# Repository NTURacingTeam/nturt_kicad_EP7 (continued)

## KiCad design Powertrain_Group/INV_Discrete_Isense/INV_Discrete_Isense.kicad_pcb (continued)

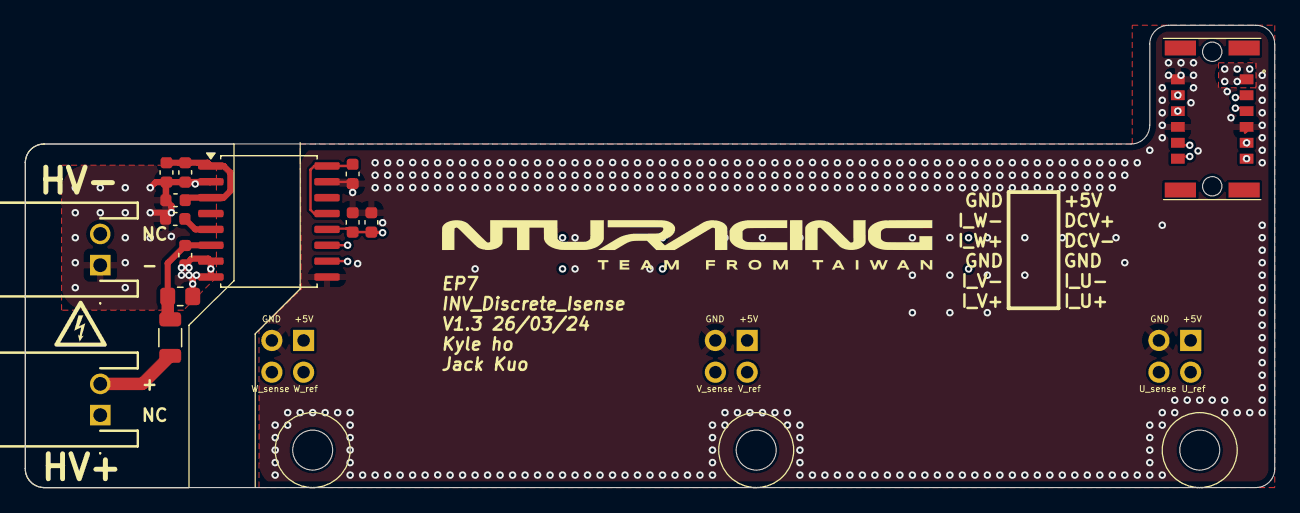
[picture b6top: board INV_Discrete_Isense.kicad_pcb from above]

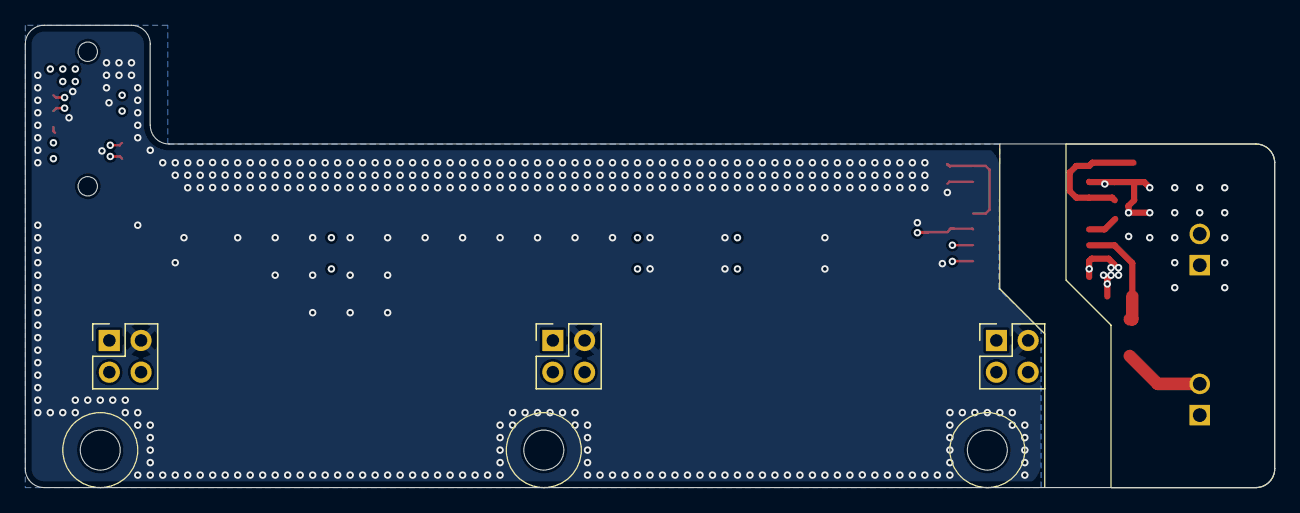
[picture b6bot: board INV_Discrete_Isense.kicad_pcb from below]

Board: 4 copper layers, 100.0 x 37.0 mm, 20 parts (3 on the bottom side), 16 nets.

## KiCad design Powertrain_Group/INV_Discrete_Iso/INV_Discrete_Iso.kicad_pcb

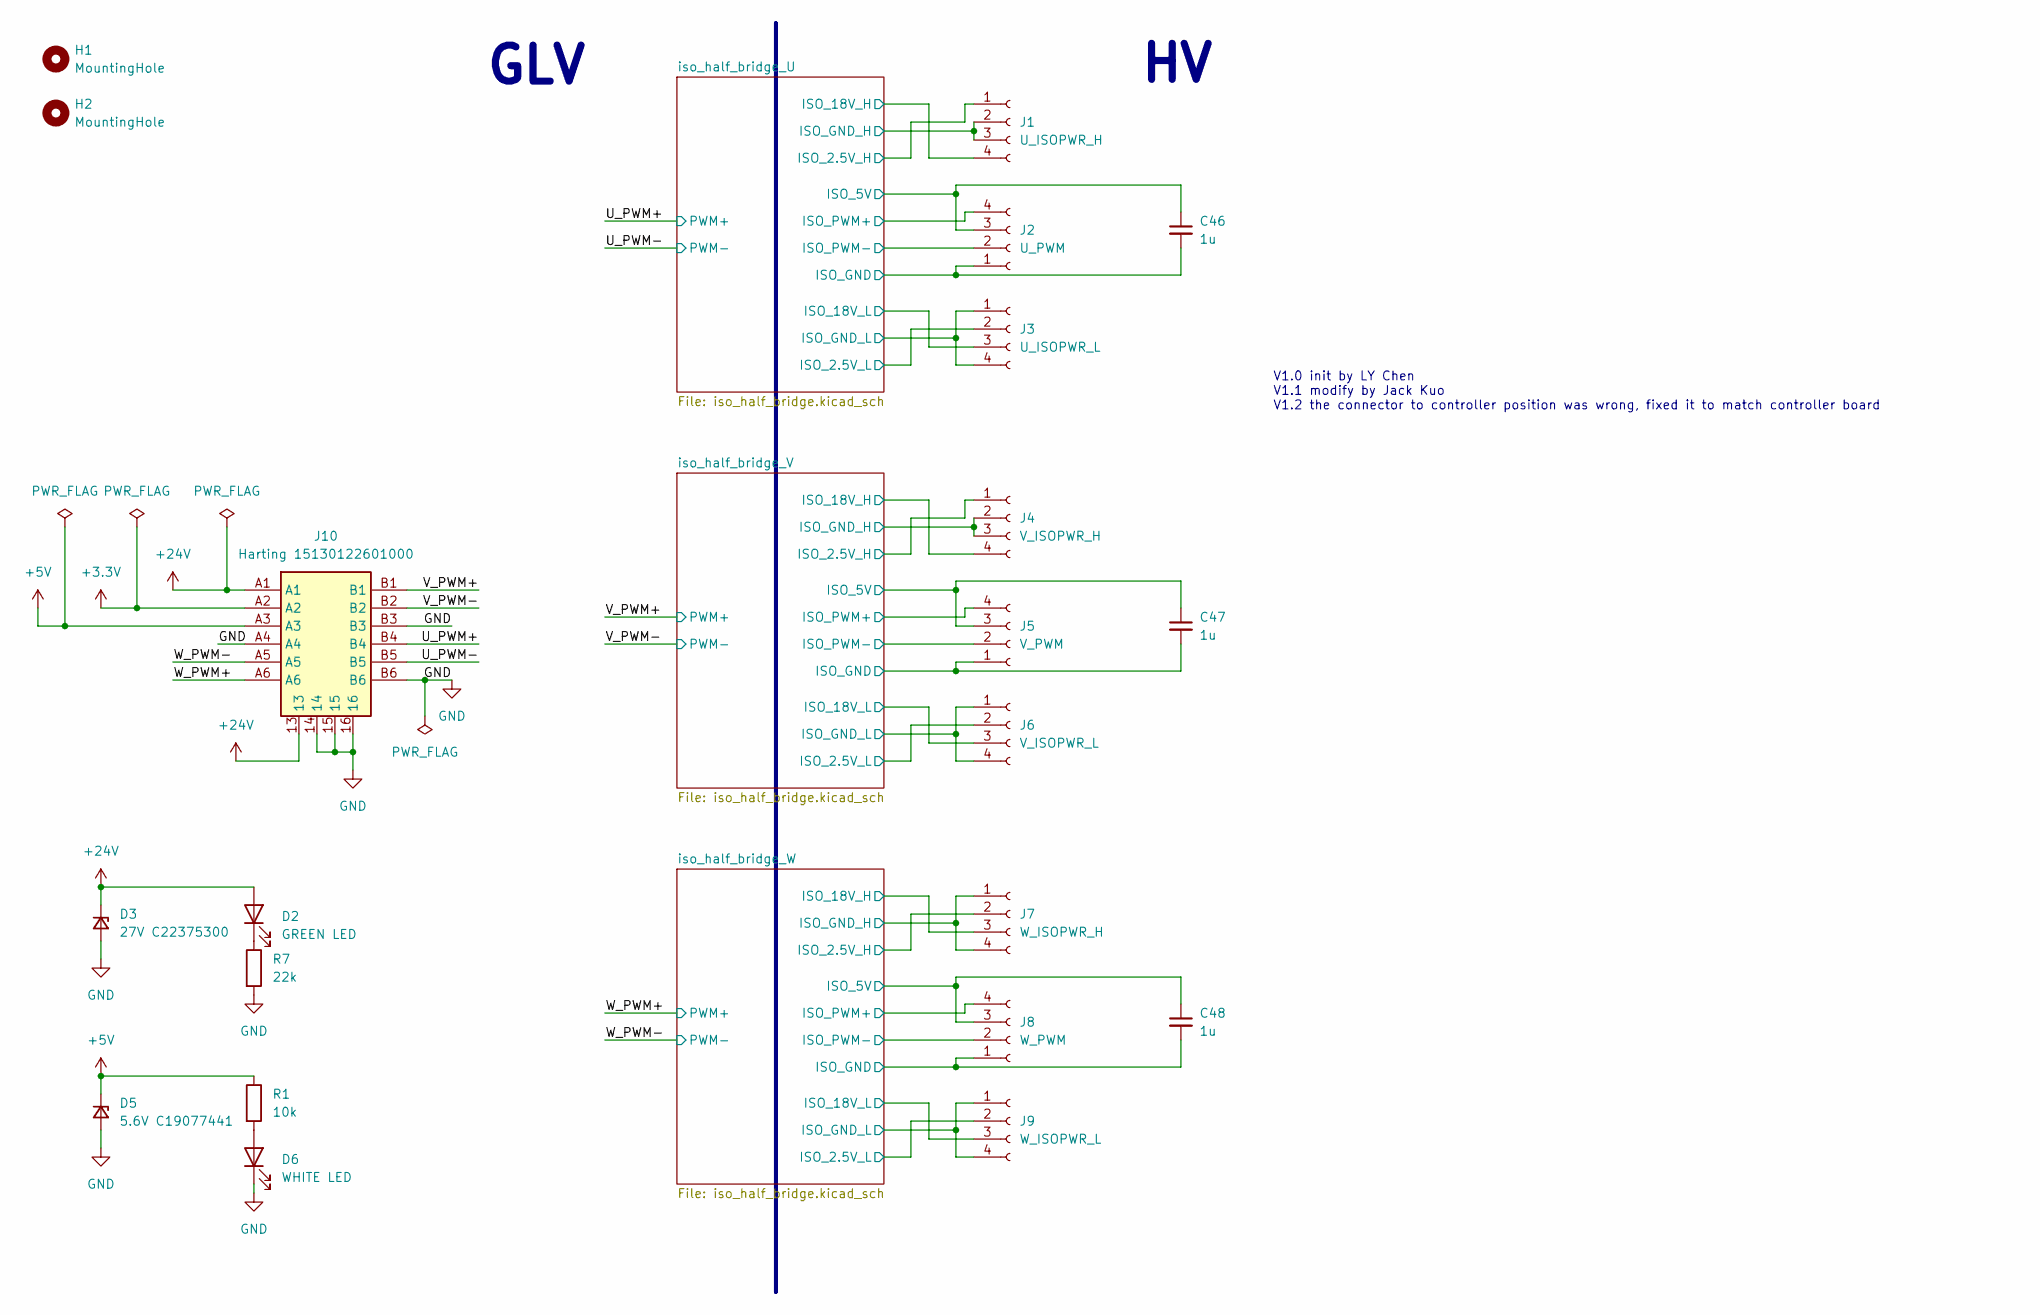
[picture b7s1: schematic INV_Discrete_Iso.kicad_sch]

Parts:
C46, C47, C48: 1u; C_0603_1608Metric
D2: GREEN LED; LED_0603_1608Metric
D3: 27V C22375300; D_SOD-323
D5: 5.6V C19077441; D_SOD-323
D6: WHITE LED; LED_0603_1608Metric
H1, H2: MountingHole; MountingHole_3.2mm_M3
J1: U_ISOPWR_H; PinSocket_2x02_P2.54mm_Vertical_SMD
J2: U_PWM; PinSocket_2x02_P2.54mm_Vertical_SMD
J3: U_ISOPWR_L; PinSocket_2x02_P2.54mm_Vertical_SMD
J4: V_ISOPWR_H; PinSocket_2x02_P2.54mm_Vertical_SMD
J5: V_PWM; PinSocket_2x02_P2.54mm_Vertical_SMD
J6: V_ISOPWR_L; PinSocket_2x02_P2.54mm_Vertical_SMD
J7: W_ISOPWR_H; PinSocket_2x02_P2.54mm_Vertical_SMD
J8: W_PWM; PinSocket_2x02_P2.54mm_Vertical_SMD
J9: W_ISOPWR_L; PinSocket_2x02_P2.54mm_Vertical_SMD
J10: Harting 15130122601000; Harting_15130122601000; Mouser Part Number 617-15130122601000
R1: 10k; R_0402_1005Metric
R7: 22k; R_0402_1005Metric

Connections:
+3.3V: J10.A2; also elsewhere on the board
+5V: D5.1 (K), J10.A3, R1.1; also elsewhere on the board
+24V: D2.2 (A), D3.1 (K), J10.13, J10.A1; also elsewhere on the board
/U_PWM+: J10.B4; also elsewhere on the board
/U_PWM-: J10.B5; also elsewhere on the board
/V_PWM+: J10.B1; also elsewhere on the board
/V_PWM-: J10.B2; also elsewhere on the board
/W_PWM+: J10.A6; also elsewhere on the board
/W_PWM-: J10.A5; also elsewhere on the board
/iso_half_bridge_U/ISO_2.5V_H: J1.1; also elsewhere on the board
/iso_half_bridge_U/ISO_2.5V_L: J3.2; also elsewhere on the board
/iso_half_bridge_U/ISO_5V: C46.1, J2.3; also elsewhere on the board
/iso_half_bridge_U/ISO_18V_H: J1.4; also elsewhere on the board
/iso_half_bridge_U/ISO_18V_L: J3.3; also elsewhere on the board
/iso_half_bridge_U/ISO_GND: C46.2, J2.1; also elsewhere on the board
/iso_half_bridge_U/ISO_GND_H: J1.2, J1.3; also elsewhere on the board
/iso_half_bridge_U/ISO_GND_L: J3.1, J3.4; also elsewhere on the board
/iso_half_bridge_U/ISO_PWM+: J2.4; also elsewhere on the board
/iso_half_bridge_U/ISO_PWM-: J2.2; also elsewhere on the board
/iso_half_bridge_V/ISO_2.5V_H: J4.1; also elsewhere on the board
/iso_half_bridge_V/ISO_2.5V_L: J6.2; also elsewhere on the board
/iso_half_bridge_V/ISO_5V: C47.1, J5.3; also elsewhere on the board
/iso_half_bridge_V/ISO_18V_H: J4.4; also elsewhere on the board
/iso_half_bridge_V/ISO_18V_L: J6.3; also elsewhere on the board
/iso_half_bridge_V/ISO_GND: C47.2, J5.1; also elsewhere on the board
/iso_half_bridge_V/ISO_GND_H: J4.2, J4.3; also elsewhere on the board
/iso_half_bridge_V/ISO_GND_L: J6.1, J6.4; also elsewhere on the board
/iso_half_bridge_V/ISO_PWM+: J5.4; also elsewhere on the board
/iso_half_bridge_V/ISO_PWM-: J5.2; also elsewhere on the board
/iso_half_bridge_W/ISO_2.5V_H: J7.2; also elsewhere on the board
/iso_half_bridge_W/ISO_2.5V_L: J9.2; also elsewhere on the board
/iso_half_bridge_W/ISO_5V: C48.1, J8.3; also elsewhere on the board
/iso_half_bridge_W/ISO_18V_H: J7.3; also elsewhere on the board
/iso_half_bridge_W/ISO_18V_L: J9.3; also elsewhere on the board
/iso_half_bridge_W/ISO_GND: C48.2, J8.1; also elsewhere on the board
/iso_half_bridge_W/ISO_GND_H: J7.1, J7.4; also elsewhere on the board
/iso_half_bridge_W/ISO_GND_L: J9.1, J9.4; also elsewhere on the board
/iso_half_bridge_W/ISO_PWM+: J8.4; also elsewhere on the board
/iso_half_bridge_W/ISO_PWM-: J8.2; also elsewhere on the board
GND: D3.2 (A), D5.2 (A), D6.1 (K), J10.14, J10.15, J10.16, J10.A4, J10.B3, J10.B6, R7.2; also elsewhere on the board
unnamed: D2.1 (K), R7.1
unnamed: D6.2 (A), R1.2

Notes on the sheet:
V1.0 init by LY Chen V1.1 modify by Jack Kuo V1.2 the connector to controller position was wrong, fixed it to match controller board
GLV

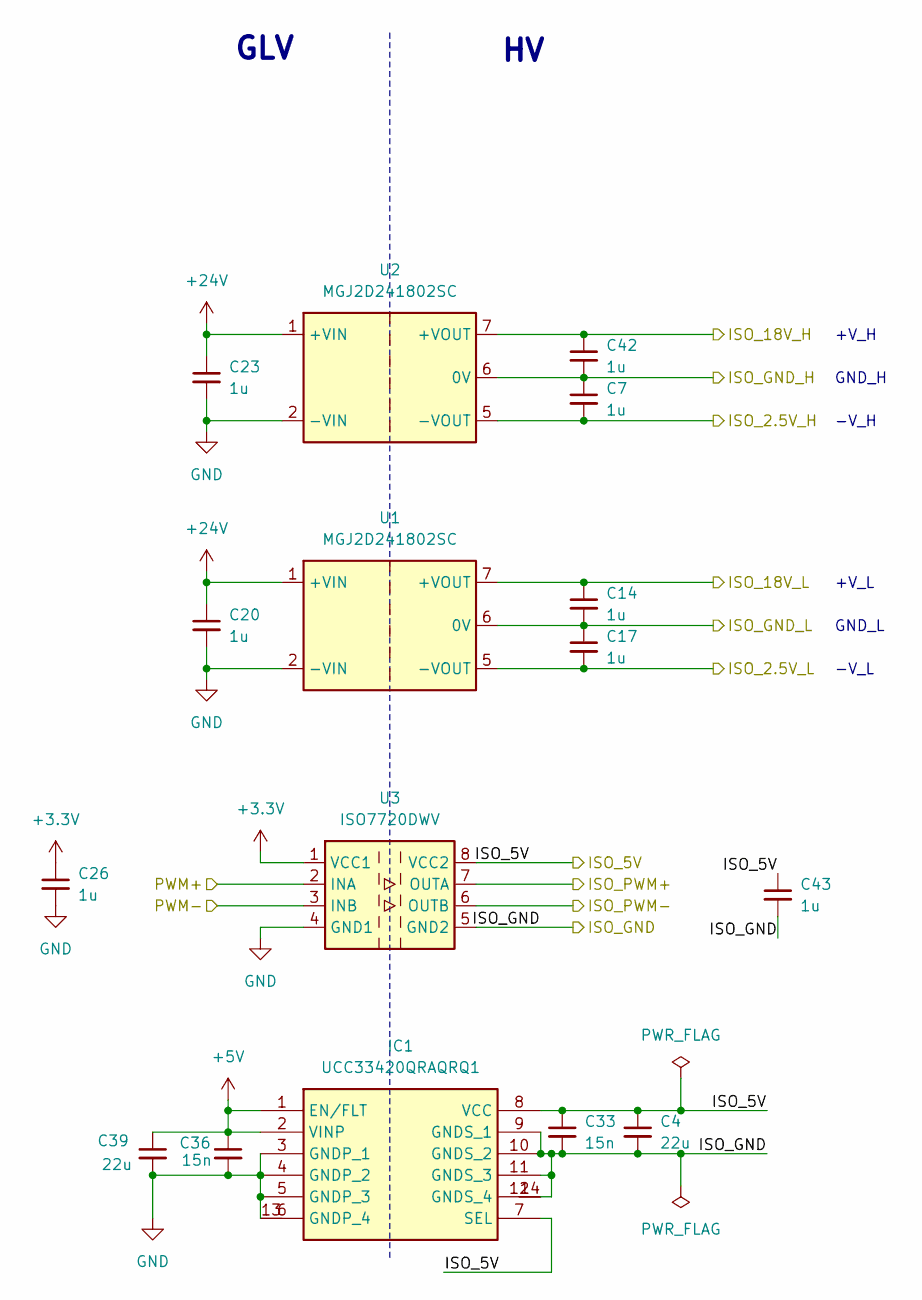
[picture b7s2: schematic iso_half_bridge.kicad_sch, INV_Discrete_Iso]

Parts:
C4, C39: 22u; C_0805_2012Metric
C7, C14, C17, C42: 1u; C_0603_1608Metric_Pad1.08x0.95mm_HandSolder
C20, C23, C26, C43: 1u; C_0603_1608Metric
C33, C36: 15n; C_0603_1608Metric_Pad1.08x0.95mm_HandSolder
IC1: UCC33420QRAQRQ1; UCC33020; Mouser Part Number 595-UCC33420QRAQRQ1
U1, U2: MGJ2D241802SC; Converter_DCDC_Murata_MGJ2DxxxxxxSC_THT
U3: ISO7720DWV; SOIC-8_7.5x5.85mm_P1.27mm

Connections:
+3.3V: C26.1, U3.1 (VCC1); also elsewhere on the board
+5V: C36.1, C39.1, IC1.1 (EN/FLT), IC1.2 (VINP); also elsewhere on the board
+24V: C20.1, C23.1, U1.1 (+VIN), U2.1 (+VIN); also elsewhere on the board
/U_PWM+: U3.2 (INA); also elsewhere on the board
/U_PWM-: U3.3 (INB); also elsewhere on the board
/iso_half_bridge_U/ISO_2.5V_H: C7.2, U2.5 (-VOUT); also elsewhere on the board
/iso_half_bridge_U/ISO_2.5V_L: C17.2, U1.5 (-VOUT); also elsewhere on the board
/iso_half_bridge_U/ISO_5V: C4.1, C33.1, C43.1, IC1.7 (SEL), IC1.8 (VCC), U3.8 (VCC2); also elsewhere on the board
/iso_half_bridge_U/ISO_18V_H: C42.1, U2.7 (+VOUT); also elsewhere on the board
/iso_half_bridge_U/ISO_18V_L: C14.1, U1.7 (+VOUT); also elsewhere on the board
/iso_half_bridge_U/ISO_GND: C4.2, C33.2, C43.2, IC1.9 (GNDS_1), IC1.10 (GNDS_2), IC1.11 (GNDS_3), IC1.12 (GNDS_4), IC1.14, U3.5 (GND2); also elsewhere on the board
/iso_half_bridge_U/ISO_GND_H: C7.1, C42.2, U2.6 (0V); also elsewhere on the board
/iso_half_bridge_U/ISO_GND_L: C14.2, C17.1, U1.6 (0V); also elsewhere on the board
/iso_half_bridge_U/ISO_PWM+: U3.7 (OUTA); also elsewhere on the board
/iso_half_bridge_U/ISO_PWM-: U3.6 (OUTB); also elsewhere on the board
GND: C20.2, C23.2, C26.2, C36.2, C39.2, IC1.3 (GNDP_1), IC1.4 (GNDP_2), IC1.5 (GNDP_3), IC1.6 (GNDP_4), IC1.13, U1.2 (-VIN), U2.2 (-VIN), U3.4 (GND1); also elsewhere on the board

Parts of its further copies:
C3, C6, C8, C24, C27, C28, C44, C45: 1u; C_0603_1608Metric
C5, C18, C25, C37: 22u; C_0805_2012Metric
C9, C10, C29, C30: 15n; C_0603_1608Metric_Pad1.08x0.95mm_HandSolder
C12, C13, C15, C16, C31, C32, C34, C35: 1u; C_0603_1608Metric_Pad1.08x0.95mm_HandSolder
IC2, IC4: UCC33420QRAQRQ1; UCC33020; Mouser Part Number 595-UCC33420QRAQRQ1
U4, U5, U7, U8: MGJ2D241802SC; Converter_DCDC_Murata_MGJ2DxxxxxxSC_THT
U6, U9: ISO7720DWV; SOIC-8_7.5x5.85mm_P1.27mm

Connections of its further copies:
+3.3V: C3.1, C24.1, U6.1 (VCC1), U9.1 (VCC1); also elsewhere on the board
+5V: C5.1, C9.1, C25.1, C29.1, IC2.1 (EN/FLT), IC2.2 (VINP), IC4.1 (EN/FLT), IC4.2 (VINP); also elsewhere on the board
+24V: C6.1, C8.1, C27.1, C28.1, U4.1 (+VIN), U5.1 (+VIN), U7.1 (+VIN), U8.1 (+VIN); also elsewhere on the board
/V_PWM+: U6.2 (INA); also elsewhere on the board
/V_PWM-: U6.3 (INB); also elsewhere on the board
/W_PWM+: U9.2 (INA); also elsewhere on the board
/W_PWM-: U9.3 (INB); also elsewhere on the board
/iso_half_bridge_V/ISO_2.5V_H: C13.2, U4.5 (-VOUT); also elsewhere on the board
/iso_half_bridge_V/ISO_2.5V_L: C16.2, U5.5 (-VOUT); also elsewhere on the board
/iso_half_bridge_V/ISO_5V: C10.1, C18.1, C44.1, IC2.7 (SEL), IC2.8 (VCC), U6.8 (VCC2); also elsewhere on the board
/iso_half_bridge_V/ISO_18V_H: C12.1, U4.7 (+VOUT); also elsewhere on the board
/iso_half_bridge_V/ISO_18V_L: C15.1, U5.7 (+VOUT); also elsewhere on the board
/iso_half_bridge_V/ISO_GND: C10.2, C18.2, C44.2, IC2.9 (GNDS_1), IC2.10 (GNDS_2), IC2.11 (GNDS_3), IC2.12 (GNDS_4), IC2.14, U6.5 (GND2); also elsewhere on the board
/iso_half_bridge_V/ISO_GND_H: C12.2, C13.1, U4.6 (0V); also elsewhere on the board
/iso_half_bridge_V/ISO_GND_L: C15.2, C16.1, U5.6 (0V); also elsewhere on the board
/iso_half_bridge_V/ISO_PWM+: U6.7 (OUTA); also elsewhere on the board
/iso_half_bridge_V/ISO_PWM-: U6.6 (OUTB); also elsewhere on the board
/iso_half_bridge_W/ISO_2.5V_H: C32.2, U7.5 (-VOUT); also elsewhere on the board
/iso_half_bridge_W/ISO_2.5V_L: C35.2, U8.5 (-VOUT); also elsewhere on the board
/iso_half_bridge_W/ISO_5V: C30.1, C37.1, C45.1, IC4.7 (SEL), IC4.8 (VCC), U9.8 (VCC2); also elsewhere on the board
/iso_half_bridge_W/ISO_18V_H: C31.1, U7.7 (+VOUT); also elsewhere on the board
/iso_half_bridge_W/ISO_18V_L: C34.1, U8.7 (+VOUT); also elsewhere on the board
/iso_half_bridge_W/ISO_GND: C30.2, C37.2, C45.2, IC4.9 (GNDS_1), IC4.10 (GNDS_2), IC4.11 (GNDS_3), IC4.12 (GNDS_4), IC4.14, U9.5 (GND2); also elsewhere on the board
/iso_half_bridge_W/ISO_GND_H: C31.2, C32.1, U7.6 (0V); also elsewhere on the board
/iso_half_bridge_W/ISO_GND_L: C34.2, C35.1, U8.6 (0V); also elsewhere on the board
/iso_half_bridge_W/ISO_PWM+: U9.7 (OUTA); also elsewhere on the board
/iso_half_bridge_W/ISO_PWM-: U9.6 (OUTB); also elsewhere on the board
GND: C3.2, C5.2, C6.2, C8.2, C9.2, C24.2, C25.2, C27.2, C28.2, C29.2, IC2.3 (GNDP_1), IC2.4 (GNDP_2), IC2.5 (GNDP_3), IC2.6 (GNDP_4), IC2.13, IC4.3 (GNDP_1), IC4.4 (GNDP_2), IC4.5 (GNDP_3), IC4.6 (GNDP_4), IC4.13, U4.2 (-VIN), U5.2 (-VIN), U6.4 (GND1), U7.2 (-VIN), U8.2 (-VIN), U9.4 (GND1); also elsewhere on the board

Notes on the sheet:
-V_L
GND_H
+V_H
GND_L
GLV
+V_L
-V_H

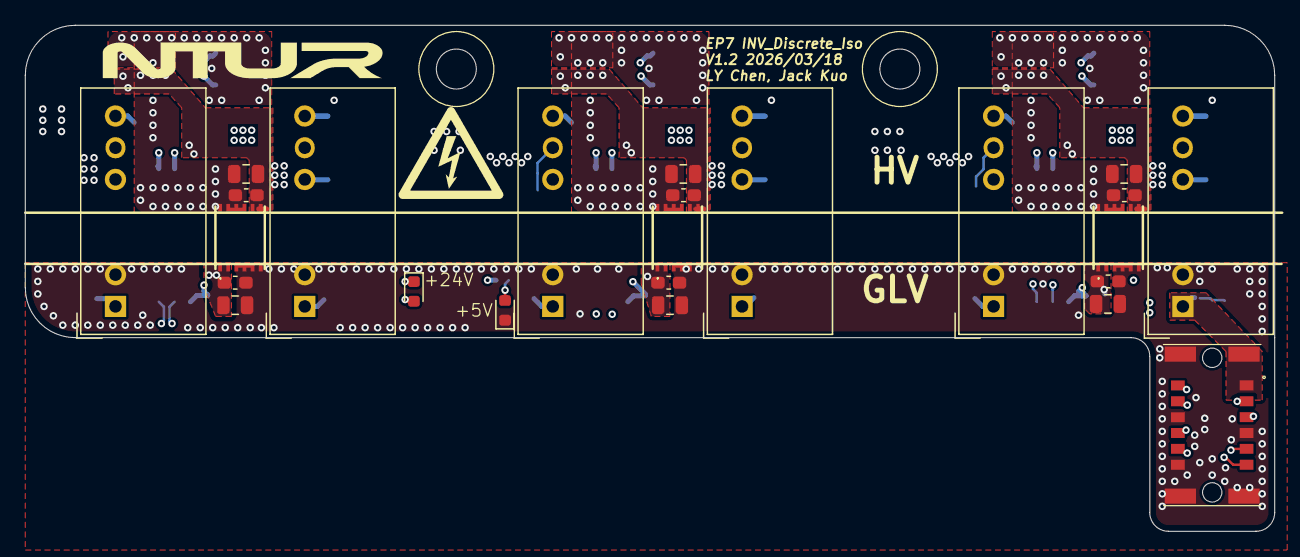
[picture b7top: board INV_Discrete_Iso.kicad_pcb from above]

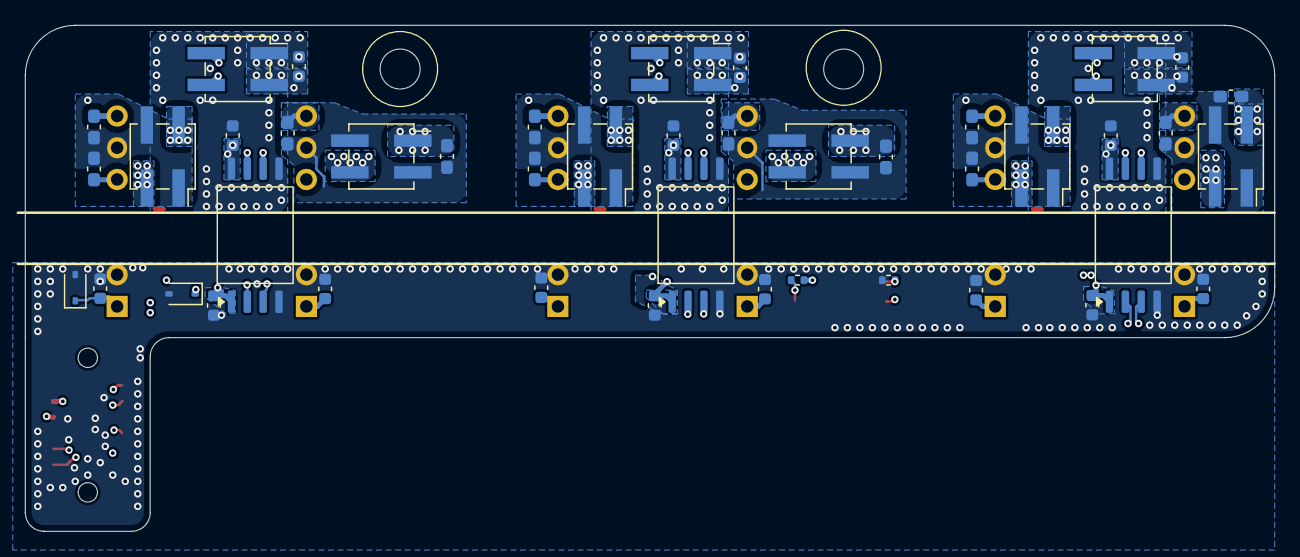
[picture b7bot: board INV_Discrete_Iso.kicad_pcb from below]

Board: 4 copper layers, 100.0 x 40.5 mm, 69 parts (43 on the bottom side), 42 nets.

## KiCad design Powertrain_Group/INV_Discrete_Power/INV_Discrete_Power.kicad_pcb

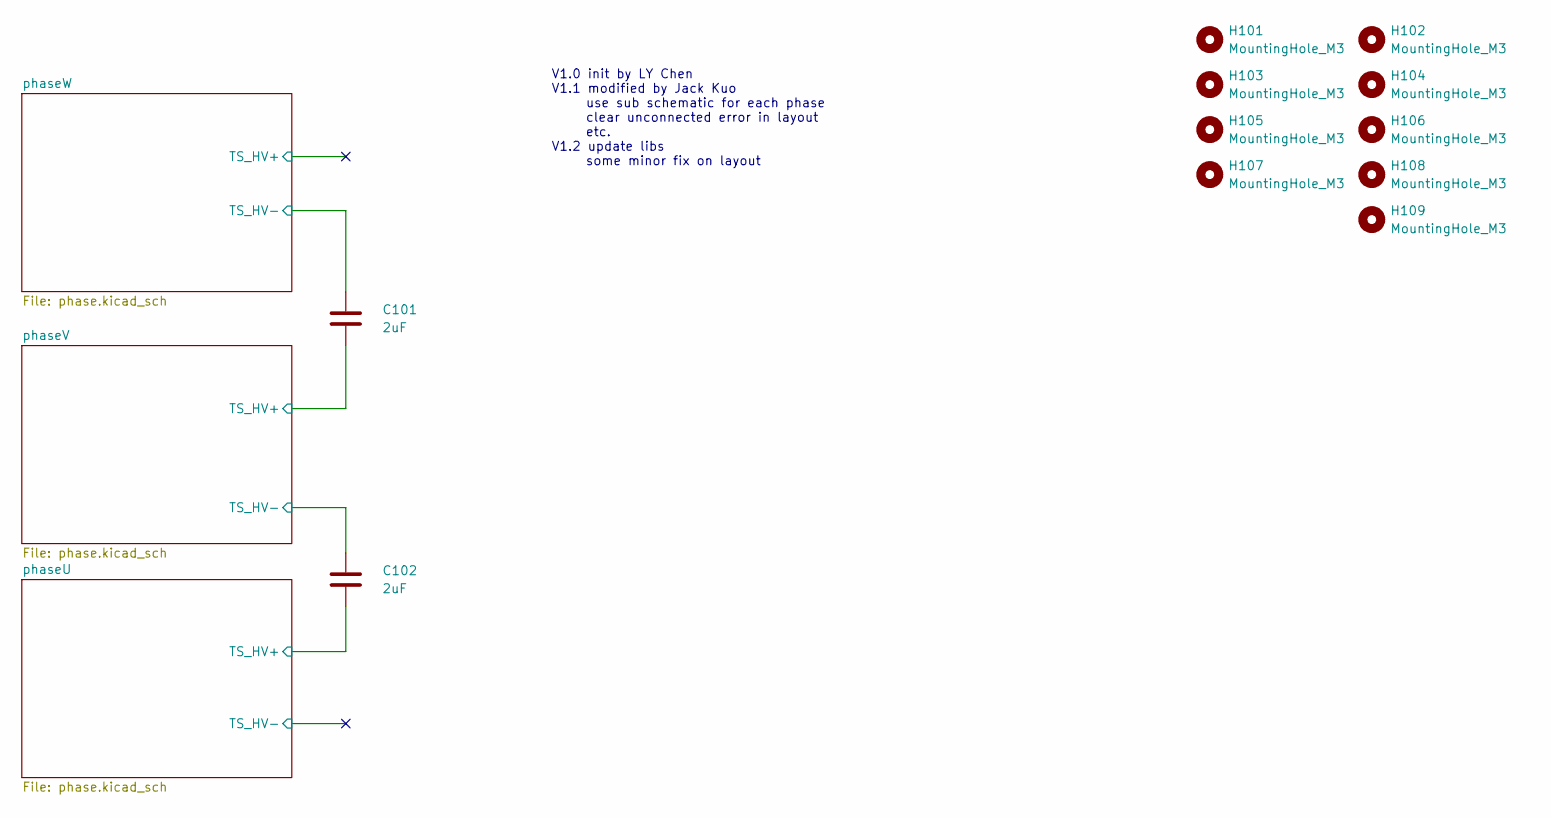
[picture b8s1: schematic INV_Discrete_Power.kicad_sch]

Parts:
C101, C102: 2uF; TDK_Ceralink_FA2
H101, H102, H103, H104, H105, H106, H107, H108, H109: MountingHole_M3; MountingHole_3.2mm_M3_ISO14580

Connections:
/phaseU/TS_HV+: C102.2; also elsewhere on the board
/phaseV/TS_HV+: C101.2; also elsewhere on the board
/phaseV/TS_HV-: C102.1; also elsewhere on the board
/phaseW/TS_HV-: C101.1; also elsewhere on the board

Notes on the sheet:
V1.0 init by LY Chen V1.1 modified by Jack Kuo use sub schematic for each phase clear unconnected error in layout etc. V1.2 update libs some minor fix on layout

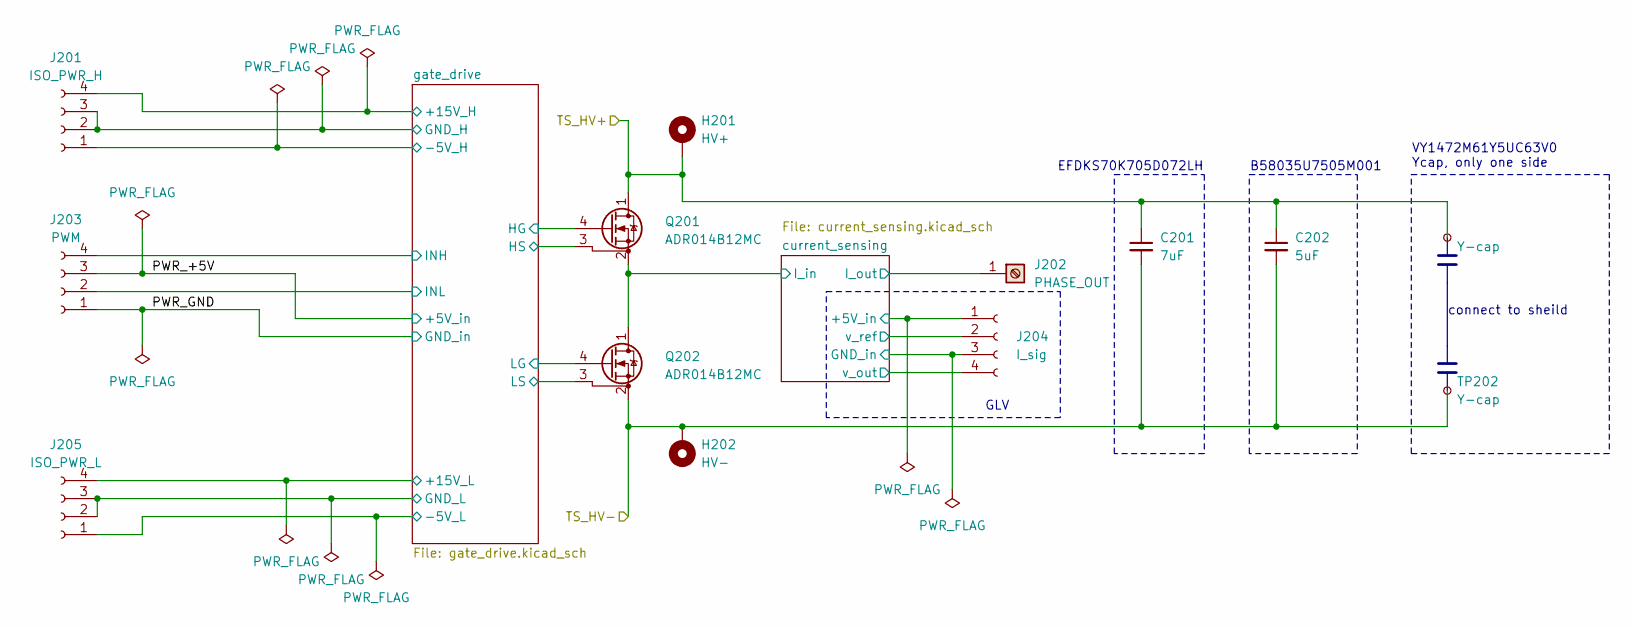
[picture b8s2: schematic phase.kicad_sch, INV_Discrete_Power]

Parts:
C201: 7uF; C_Rect_L33.0mm_W15.0mm_P27.50mm_MKS4
C202: 5uF; TDK_Ceralink_FA10
H201: HV+; MountingHole_3.2mm_M3_Pad_Via
H202: HV-; MountingHole_3.2mm_M3_Pad_Via
J201: ISO_PWR_H; PinHeader_2x02_P2.54mm_Vertical
J202: PHASE_OUT; Wuerth_REDCUBE-THR_WP-THRSH_74651195_THR
J203: PWM; PinHeader_2x02_P2.54mm_Vertical
J204: I_sig; PinHeader_2x02_P2.54mm_Vertical
J205: ISO_PWR_L; PinHeader_2x02_P2.54mm_Vertical
Q201, Q202: ADR014B12MC; TO-247-4_Horizontal_TabUp_NoHole
TP201, TP202: Y-cap; TestPoint_THTPad_D1.5mm_Drill0.7mm

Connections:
/phaseW/PWR_+5V: J203.3; also elsewhere on the board
/phaseW/PWR_GND: J203.1; also elsewhere on the board
/phaseW/TS_HV+: C201.1, C202.1, H201.1, Q201.1 (D), TP201.1
/phaseW/TS_HV-: C201.2, C202.2, H202.1, Q202.2 (S), TP202.1; also elsewhere on the board
/phaseW/current_sensing/+5V_in: J204.1; also elsewhere on the board
/phaseW/current_sensing/GND_in: J204.3; also elsewhere on the board
/phaseW/current_sensing/I_in: Q201.2 (S), Q202.1 (D); also elsewhere on the board
/phaseW/current_sensing/I_out: J202.1; also elsewhere on the board
/phaseW/current_sensing/v_out: J204.4; also elsewhere on the board
/phaseW/current_sensing/v_ref: J204.2; also elsewhere on the board
/phaseW/gate_drive/+15V_H: J201.4; also elsewhere on the board
/phaseW/gate_drive/+15V_L: J205.4; also elsewhere on the board
/phaseW/gate_drive/-5V_H: J201.1; also elsewhere on the board
/phaseW/gate_drive/-5V_L: J205.1; also elsewhere on the board
/phaseW/gate_drive/GND_H: J201.2, J201.3, Q201.3 (DS); also elsewhere on the board
/phaseW/gate_drive/GND_L: J205.2, J205.3, Q202.3 (DS); also elsewhere on the board
/phaseW/gate_drive/HG: Q201.4 (G); also elsewhere on the board
/phaseW/gate_drive/INH: J203.4; also elsewhere on the board
/phaseW/gate_drive/INL: J203.2; also elsewhere on the board
/phaseW/gate_drive/LG: Q202.4 (G); also elsewhere on the board

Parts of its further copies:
C301, C401: 7uF; C_Rect_L33.0mm_W15.0mm_P27.50mm_MKS4
C302, C402: 5uF; TDK_Ceralink_FA10
H301, H401: HV+; MountingHole_3.2mm_M3_Pad_Via
H302, H402: HV-; MountingHole_3.2mm_M3_Pad_Via
J301, J401: ISO_PWR_H; PinHeader_2x02_P2.54mm_Vertical
J302, J402: PHASE_OUT; Wuerth_REDCUBE-THR_WP-THRSH_74651195_THR
J303, J403: PWM; PinHeader_2x02_P2.54mm_Vertical
J304, J404: I_sig; PinHeader_2x02_P2.54mm_Vertical
J305, J405: ISO_PWR_L; PinHeader_2x02_P2.54mm_Vertical
Q301, Q302, Q401, Q402: ADR014B12MC; TO-247-4_Horizontal_TabUp_NoHole
TP301, TP302, TP401, TP402: Y-cap; TestPoint_THTPad_D1.5mm_Drill0.7mm

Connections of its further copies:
/phaseU/PWR_+5V: J403.3; also elsewhere on the board
/phaseU/PWR_GND: J403.1; also elsewhere on the board
/phaseU/TS_HV+: C401.1, C402.1, H401.1, Q401.1 (D), TP401.1; also elsewhere on the board
/phaseU/TS_HV-: C401.2, C402.2, H402.1, Q402.2 (S), TP402.1
/phaseU/current_sensing/+5V_in: J404.1; also elsewhere on the board
/phaseU/current_sensing/GND_in: J404.3; also elsewhere on the board
/phaseU/current_sensing/I_in: Q401.2 (S), Q402.1 (D); also elsewhere on the board
/phaseU/current_sensing/I_out: J402.1; also elsewhere on the board
/phaseU/current_sensing/v_out: J404.4; also elsewhere on the board
/phaseU/current_sensing/v_ref: J404.2; also elsewhere on the board
/phaseU/gate_drive/+15V_H: J401.4; also elsewhere on the board
/phaseU/gate_drive/+15V_L: J405.4; also elsewhere on the board
/phaseU/gate_drive/-5V_H: J401.1; also elsewhere on the board
/phaseU/gate_drive/-5V_L: J405.1; also elsewhere on the board
/phaseU/gate_drive/GND_H: J401.2, J401.3, Q401.3 (DS); also elsewhere on the board
/phaseU/gate_drive/GND_L: J405.2, J405.3, Q402.3 (DS); also elsewhere on the board
/phaseU/gate_drive/HG: Q401.4 (G); also elsewhere on the board
/phaseU/gate_drive/INH: J403.4; also elsewhere on the board
/phaseU/gate_drive/INL: J403.2; also elsewhere on the board
/phaseU/gate_drive/LG: Q402.4 (G); also elsewhere on the board
/phaseV/PWR_+5V: J303.3; also elsewhere on the board
/phaseV/PWR_GND: J303.1; also elsewhere on the board
/phaseV/TS_HV+: C301.1, C302.1, H301.1, Q301.1 (D), TP301.1; also elsewhere on the board
/phaseV/TS_HV-: C301.2, C302.2, H302.1, Q302.2 (S), TP302.1; also elsewhere on the board
/phaseV/current_sensing/+5V_in: J304.1; also elsewhere on the board
/phaseV/current_sensing/GND_in: J304.3; also elsewhere on the board
/phaseV/current_sensing/I_in: Q301.2 (S), Q302.1 (D); also elsewhere on the board
/phaseV/current_sensing/I_out: J302.1; also elsewhere on the board
/phaseV/current_sensing/v_out: J304.4; also elsewhere on the board
/phaseV/current_sensing/v_ref: J304.2; also elsewhere on the board
/phaseV/gate_drive/+15V_H: J301.4; also elsewhere on the board
/phaseV/gate_drive/+15V_L: J305.4; also elsewhere on the board
/phaseV/gate_drive/-5V_H: J301.1; also elsewhere on the board
/phaseV/gate_drive/-5V_L: J305.1; also elsewhere on the board
/phaseV/gate_drive/GND_H: J301.2, J301.3, Q301.3 (DS); also elsewhere on the board
/phaseV/gate_drive/GND_L: J305.2, J305.3, Q302.3 (DS); also elsewhere on the board
/phaseV/gate_drive/HG: Q301.4 (G); also elsewhere on the board
/phaseV/gate_drive/INH: J303.4; also elsewhere on the board
/phaseV/gate_drive/INL: J303.2; also elsewhere on the board
/phaseV/gate_drive/LG: Q302.4 (G); also elsewhere on the board

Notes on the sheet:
GLV
VY1472M61Y5UC63V0 Ycap, only one side
B58035U7505M001
EFDKS70K705D072LH
connect to sheild

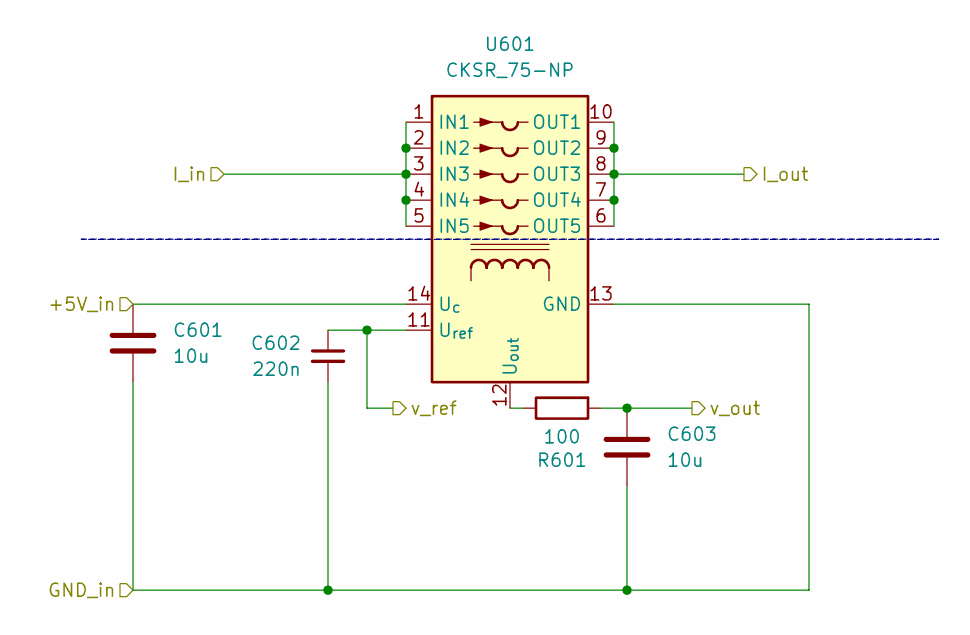
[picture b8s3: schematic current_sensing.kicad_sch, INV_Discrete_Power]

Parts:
C601, C603: 10u; C_0805_2012Metric
C602: 220n; C_0603_1608Metric
R601: 100; R_0603_1608Metric
U601: CKSR_75-NP; LEM_CKSR

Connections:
/phaseW/current_sensing/+5V_in: C601.1, U601.14 (U_{c}); also elsewhere on the board
/phaseW/current_sensing/GND_in: C601.2, C602.2, C603.2, U601.13 (GND); also elsewhere on the board
/phaseW/current_sensing/I_in: U601.1 (IN1), U601.2 (IN2), U601.3 (IN3), U601.4 (IN4), U601.5 (IN5); also elsewhere on the board
/phaseW/current_sensing/I_out: U601.6 (OUT5), U601.7 (OUT4), U601.8 (OUT3), U601.9 (OUT2), U601.10 (OUT1); also elsewhere on the board
/phaseW/current_sensing/v_out: C603.1, R601.2; also elsewhere on the board
/phaseW/current_sensing/v_ref: C602.1, U601.11 (U_{ref}); also elsewhere on the board
unnamed: R601.1, U601.12 (U_{out})

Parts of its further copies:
C801, C803, C1001, C1003: 10u; C_0805_2012Metric
C802, C1002: 220n; C_0603_1608Metric
R801, R1001: 100; R_0603_1608Metric
U801, U1001: CKSR_75-NP; LEM_CKSR

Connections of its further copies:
/phaseU/current_sensing/+5V_in: C1001.1, U1001.14 (U_{c}); also elsewhere on the board
/phaseU/current_sensing/GND_in: C1001.2, C1002.2, C1003.2, U1001.13 (GND); also elsewhere on the board
/phaseU/current_sensing/I_in: U1001.1 (IN1), U1001.2 (IN2), U1001.3 (IN3), U1001.4 (IN4), U1001.5 (IN5); also elsewhere on the board
/phaseU/current_sensing/I_out: U1001.6 (OUT5), U1001.7 (OUT4), U1001.8 (OUT3), U1001.9 (OUT2), U1001.10 (OUT1); also elsewhere on the board
/phaseU/current_sensing/v_out: C1003.1, R1001.2; also elsewhere on the board
/phaseU/current_sensing/v_ref: C1002.1, U1001.11 (U_{ref}); also elsewhere on the board
/phaseV/current_sensing/+5V_in: C801.1, U801.14 (U_{c}); also elsewhere on the board
/phaseV/current_sensing/GND_in: C801.2, C802.2, C803.2, U801.13 (GND); also elsewhere on the board
/phaseV/current_sensing/I_in: U801.1 (IN1), U801.2 (IN2), U801.3 (IN3), U801.4 (IN4), U801.5 (IN5); also elsewhere on the board
/phaseV/current_sensing/I_out: U801.6 (OUT5), U801.7 (OUT4), U801.8 (OUT3), U801.9 (OUT2), U801.10 (OUT1); also elsewhere on the board
/phaseV/current_sensing/v_out: C803.1, R801.2; also elsewhere on the board
/phaseV/current_sensing/v_ref: C802.1, U801.11 (U_{ref}); also elsewhere on the board
unnamed: R801.1, U801.12 (U_{out})
unnamed: R1001.1, U1001.12 (U_{out})
